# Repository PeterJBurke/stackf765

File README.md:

# StackF765

An open-hardware **ArduPilot flight controller** built around the STM32F765:
two stacked 31.5 × 48 mm boards on a 20 × 20 mm mount, plus a small USB / buzzer / boot
board on a cable. Every connection except the battery and ESC power wires is a labelled 0.1 inch (Dupont) right-angle pin on the upper board: a 3 × 12 header at the front, and a 3 × 9 header at the back for motors, LED and companion-computer power.

**[3D project page](https://peterjburke.github.io/stackf765/)** ·
**[Drone viewer](https://peterjburke.github.io/stackf765/drone/)** ·
[Pinout](docs/pinout.md) · [How it works](docs/design.md) · [Order boards](docs/manufacturing.md) ·
[Assemble](docs/assembly.md) · [First power-up](docs/bringup.md) · [Firmware](docs/firmware.md) ·
[Verification](docs/verification.md)

| Upper board (flight controller) | Lower board (power) | Service board |
|---|---|---|
|  |  |  |

> **Status: design complete and verified by rule checks; no hardware has been built yet.**
> The first boards are prototypes. Use the [first power-up procedure](docs/bringup.md).

## At a glance

| | |
|---|---|
| Processor | STM32F765VIT6, 216 MHz Cortex-M7, 2 MB flash |
| Firmware | ArduPilot (Copter, Plane, Rover), board name `StackF765` |
| Sensors | ICM-45686 IMU (SPI), BMP388 barometer (I2C) |
| Battery | 2S–3S LiPo (6–13 V), 50 A continuous through a 0.5 mΩ shunt |
| Serial | 7 UARTs + USB |
| Outputs | 6 motor/servo outputs on standard 3-pin columns (signal / 5 V / ground), addressable LED |
| Video | Analog OSD (AT7456E), camera in / VTX out |
| Logging | microSD (socket under the upper board, card inserted from the left edge) |
| 5 V rails | 3 A for the flight controller and peripherals, a separate 3 A for a companion computer |
| Size | 31.5 × 48 × about 19 mm, 20 × 20 mm grommet mount |

## Pinout in brief

Front header (upper board), seen from above with the header pointing away from you:

| Row | 1 | 2 | 3 | 4 | 5 | 6 | 7 | 8 | 9 | 10 | 11 | 12 |
|---|---|---|---|---|---|---|---|---|---|---|---|---|
| front edge | G | 5V | TX6 | RX6 | G | 5V | TX7 | RX7 | G | 5V | TX8 | RX8 |
| middle | G | 4V5 | TX2 | RX2 | G | 5V | TX3 | RX3 | G | 5V | TX4 | RX4 |
| inner | G | 4V5 | TX1 | RX1 | SDA | SCL | G | 5V | CAM | G | 5V | VTX |

Rear header (upper board), looking into the pins from behind, columns left to right: `PI5V PI5V M1 M2 M3 M4 M5 M6 LED`; each column is signal / 5 V / ground from top to bottom, so a 3-pin servo plug fits directly. The lower board has no pin header.
Power pads at the rear: `BAT+ ESC+ ESC− BAT−`. Full details: [docs/pinout.md](docs/pinout.md).

## What is in this repository

| Folder | Contents |
|---|---|
| `hardware/` | KiCad 9 projects for the three boards (schematics and routed PCBs), custom footprints and 3D models |
| `fab/` | Gerbers, drill files, bills of materials and placement files, ready to upload |
| `firmware/` | ArduPilot board definition (`hwdef`), build script, prebuilt binaries |
| `docs/` | Documentation, schematic PDFs, renders, and the web pages |
| `gen/` | The Python design files the KiCad projects are generated from, and the generator |
| `tools/` | Verification scripts |
| `research/` | Part selection notes, datasheet checks, and the independent design review |

## How the design is made

The circuits are written as short Python files (`gen/upper.py`, `gen/lower.py`,
`gen/service.py`). `make` turns them into KiCad schematics and boards, places and routes
the parts, fills the copper, runs KiCad's own rule checks, and writes the fabrication files,
renders and web pages. Because one description produces both schematic and board, they cannot
drift apart, and KiCad checks that they match.

You do not need the generator to use the design: open `hardware/<board>/<board>.kicad_pro`
in KiCad 9 and work on it like any other project.

```sh
make            # regenerate everything (needs KiCad 9, Python 3, gcc)
make verify     # run all checks on the committed files
make firmware ARDUPILOT=/path/to/ardupilot
```

## Verification summary

Every board passes KiCad ERC and DRC with zero violations and zero unconnected nets, the
board matches the schematic, the 49 microcontroller pins used by the firmware are cross-checked
against the schematic, the boards are checked to fit together, and ArduPilot builds for the
board. See [docs/verification-report.md](docs/verification-report.md) for the current results
and [docs/verification.md](docs/verification.md) for what those checks do and do not cover.

## Licence

Hardware: [CERN-OHL-P v2](LICENSE-HARDWARE.txt). Software, scripts and documentation: [MIT](LICENSE).
The drone frame model and coin used in the drone viewer are third-party assets; see
`docs/drone/assets/CREDITS.txt`.

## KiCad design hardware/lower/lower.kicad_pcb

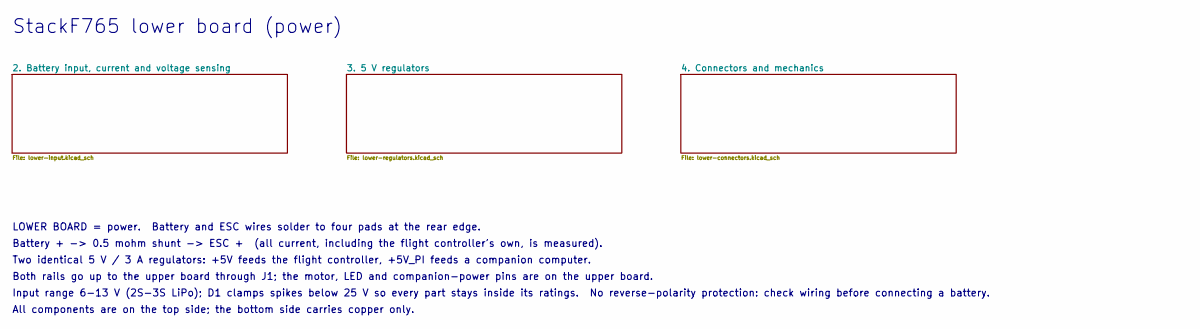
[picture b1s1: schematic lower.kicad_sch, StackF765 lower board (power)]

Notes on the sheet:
StackF765 lower board (power)
LOWER BOARD = power. Battery and ESC wires solder to four pads at the rear edge.
Battery + -> 0.5 mohm shunt -> ESC + (all current, including the flight controller's own, is measured).
Two identical 5 V / 3 A regulators: +5V feeds the flight controller, +5V_PI feeds a companion computer.
Both rails go up to the upper board through J1; the motor, LED and companion-power pins are on the upper board.
Input range 6-13 V (2S-3S LiPo); D1 clamps spikes below 25 V so every part stays inside its ratings. No reverse-polarity protection: check wiring before connecting a battery.
All components are on the top side; the bottom side carries copper only.

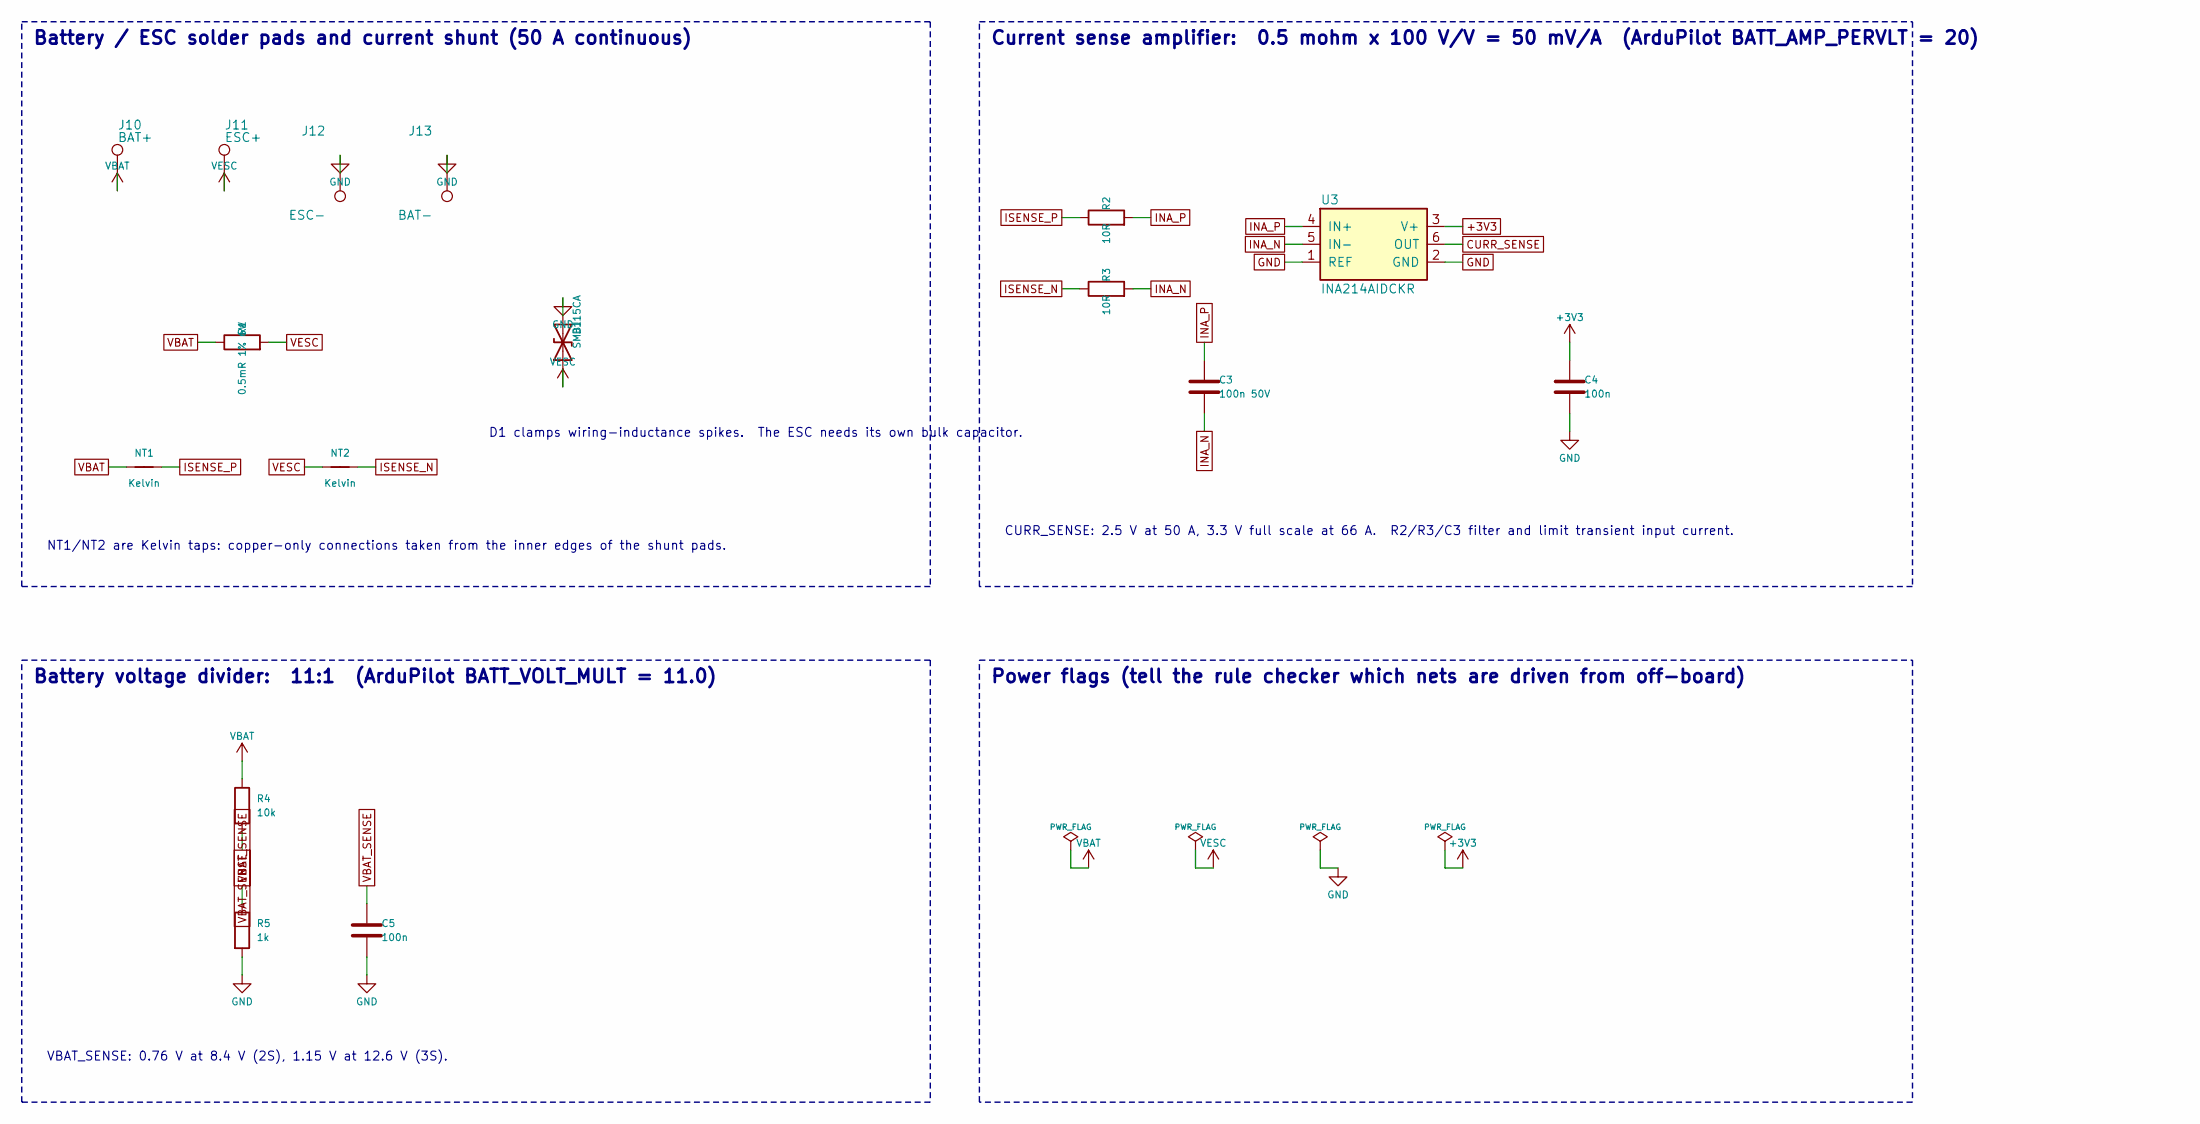
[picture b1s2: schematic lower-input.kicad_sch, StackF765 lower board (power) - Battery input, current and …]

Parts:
C3: 100n 50V; C_0402_1005Metric; MPN GRM155R71H104KE14D; LCSC C77020
C4, C5: 100n; C_0402_1005Metric; MPN CL05B104KO5NNNC; LCSC C1525
D1: SMBJ15CA; D_SMB; MPN SMBJ15CA; LCSC C169449
J10: BAT+; WirePad_5x4mm
J11: ESC+; WirePad_5x4mm
J12: ESC-; WirePad_5x4mm
J13: BAT-; WirePad_5x4mm
NT1, NT2: Kelvin; NetTie-2_SMD_Pad0.5mm
R1: 0.5mR 1% 6W; R_Shunt_2512_ASR-M-3; MPN ASR-M-3-0.5F; LCSC C469426
R2, R3: 10R; R_0402_1005Metric; MPN 0402WGF100JTCE; LCSC C25077
R4: 10k; R_0402_1005Metric; MPN 0402WGF1002TCE; LCSC C25744
R5: 1k; R_0402_1005Metric; MPN 0402WGF1001TCE; LCSC C11702
U3: INA214AIDCKR; SOT-363_SC-70-6; MPN INA214AIDCKR; LCSC C105240

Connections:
+3V3: C4.1, U3.3 (V+); also elsewhere on the board
CURR_SENSE: U3.6 (OUT); also elsewhere on the board
GND: C4.2, C5.2, D1.2 (A2), J12.1, J13.1, R5.2, U3.1 (REF), U3.2 (GND); also elsewhere on the board
INA_N: C3.2, R3.2, U3.5 (IN-)
INA_P: C3.1, R2.2, U3.4 (IN+)
ISENSE_N: NT2.2, R3.1
ISENSE_P: NT1.2, R2.1
VBAT: J10.1, NT1.1, R1.1, R4.1
VBAT_SENSE: C5.1, R4.2, R5.1; also elsewhere on the board
VESC: D1.1 (A1), J11.1, NT2.1, R1.2; also elsewhere on the board

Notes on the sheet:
Battery / ESC solder pads and current shunt (50 A continuous)
NT1/NT2 are Kelvin taps: copper-only connections taken from the inner edges of the shunt pads.
D1 clamps wiring-inductance spikes. The ESC needs its own bulk capacitor.
Current sense amplifier: 0.5 mohm x 100 V/V = 50 mV/A (ArduPilot BATT_AMP_PERVLT = 20)
CURR_SENSE: 2.5 V at 50 A, 3.3 V full scale at 66 A. R2/R3/C3 filter and limit transient input current.
Battery voltage divider: 11:1 (ArduPilot BATT_VOLT_MULT = 11.0)
VBAT_SENSE: 0.76 V at 8.4 V (2S), 1.15 V at 12.6 V (3S).
Power flags (tell the rule checker which nets are driven from off-board)

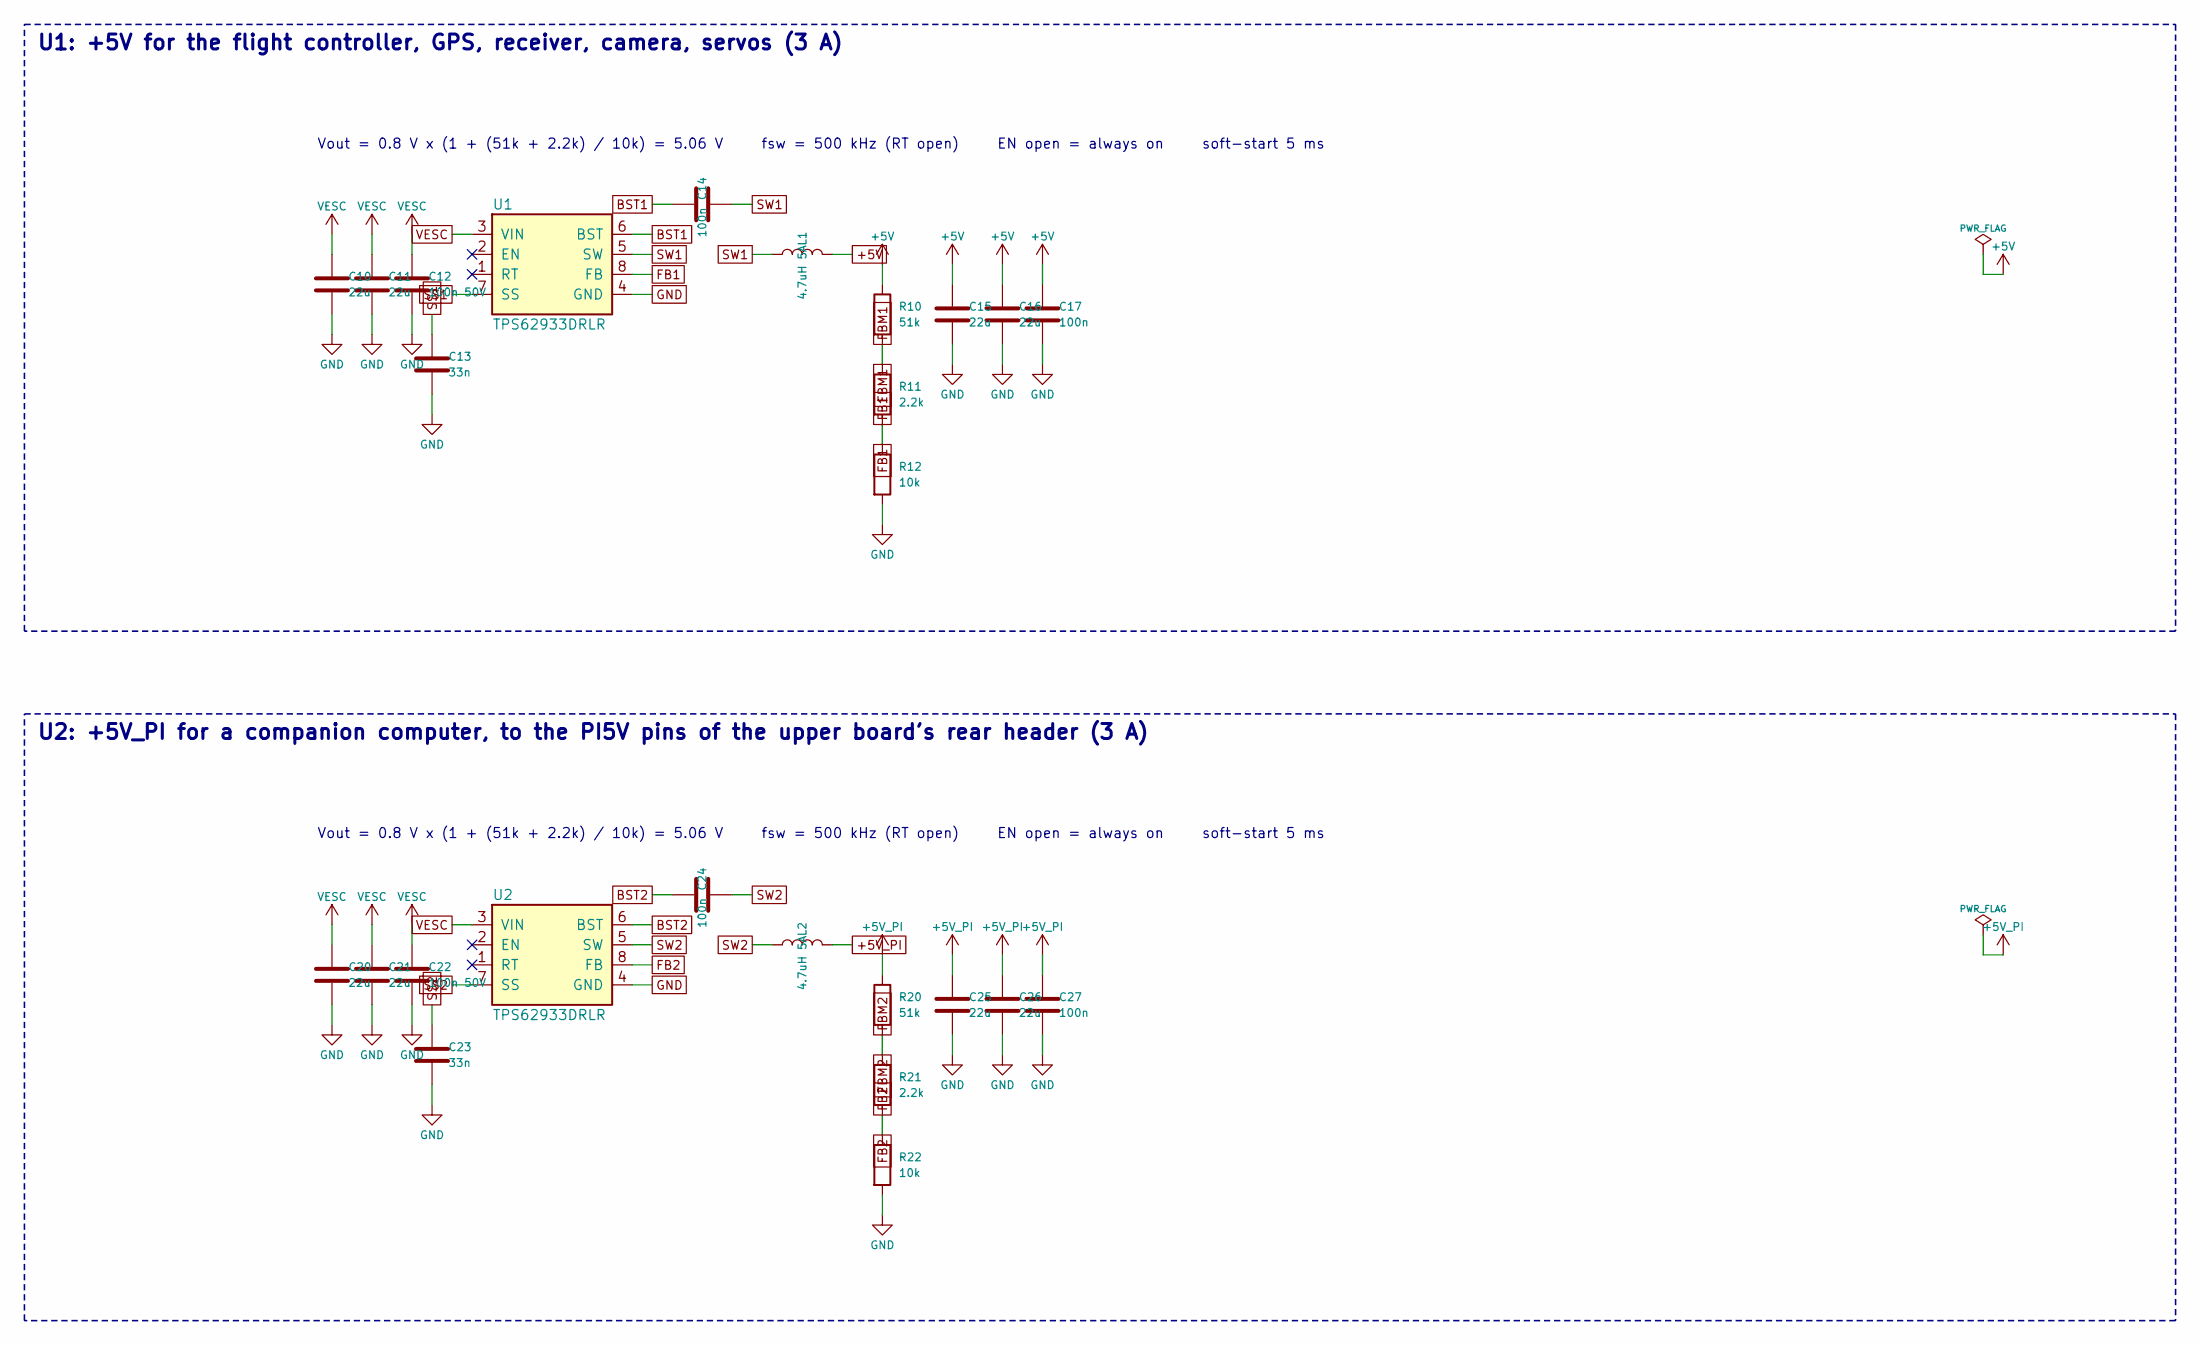
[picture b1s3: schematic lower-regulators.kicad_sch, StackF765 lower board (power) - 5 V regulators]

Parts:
C10, C11, C20, C21: 22u; C_1206_3216Metric; MPN CL31A226KAHNNNE; LCSC C12891
C12, C22: 100n 50V; C_0402_1005Metric; MPN GRM155R71H104KE14D; LCSC C77020
C13, C23: 33n; C_0402_1005Metric; MPN CC0402KRX7R9BB333; LCSC C106862
C14, C17, C24, C27: 100n; C_0402_1005Metric; MPN CL05B104KO5NNNC; LCSC C1525
C15, C16, C25, C26: 22u; C_0805_2012Metric; MPN CL21A226MAQNNNE; LCSC C45783
L1, L2: 4.7uH 5A; L_SXN_SMMS0530; MPN SMMS0530-4R7M; LCSC C181722
R10, R20: 51k; R_0402_1005Metric; MPN 0402WGF5102TCE; LCSC C25794
R11, R21: 2.2k; R_0402_1005Metric; MPN 0402WGF2201TCE; LCSC C25879
R12, R22: 10k; R_0402_1005Metric; MPN 0402WGF1002TCE; LCSC C25744
U1, U2: TPS62933DRLR; SOT-583-8; MPN TPS62933DRLR; LCSC C3200405

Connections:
+5V: C15.1, C16.1, C17.1, L1.2, R10.1; also elsewhere on the board
+5V_PI: C25.1, C26.1, C27.1, L2.2, R20.1; also elsewhere on the board
BST1: C14.1, U1.6 (BST)
BST2: C24.1, U2.6 (BST)
FB1: R11.2, R12.1, U1.8 (FB)
FB2: R21.2, R22.1, U2.8 (FB)
FBM1: R10.2, R11.1
FBM2: R20.2, R21.1
GND: C10.2, C11.2, C12.2, C13.2, C15.2, C16.2, C17.2, C20.2, C21.2, C22.2, C23.2, C25.2, C26.2, C27.2, R12.2, R22.2, U1.4 (GND), U2.4 (GND); also elsewhere on the board
SS1: C13.1, U1.7 (SS)
SS2: C23.1, U2.7 (SS)
SW1: C14.2, L1.1, U1.5 (SW)
SW2: C24.2, L2.1, U2.5 (SW)
VESC: C10.1, C11.1, C12.1, C20.1, C21.1, C22.1, U1.3 (VIN), U2.3 (VIN); also elsewhere on the board

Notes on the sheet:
U1: +5V for the flight controller, GPS, receiver, camera, servos (3 A)
Vout = 0.8 V x (1 + (51k + 2.2k) / 10k) = 5.06 V fsw = 500 kHz (RT open) EN open = always on soft-start 5 ms
U2: +5V_PI for a companion computer, to the PI5V pins of the upper board's rear header (3 A)

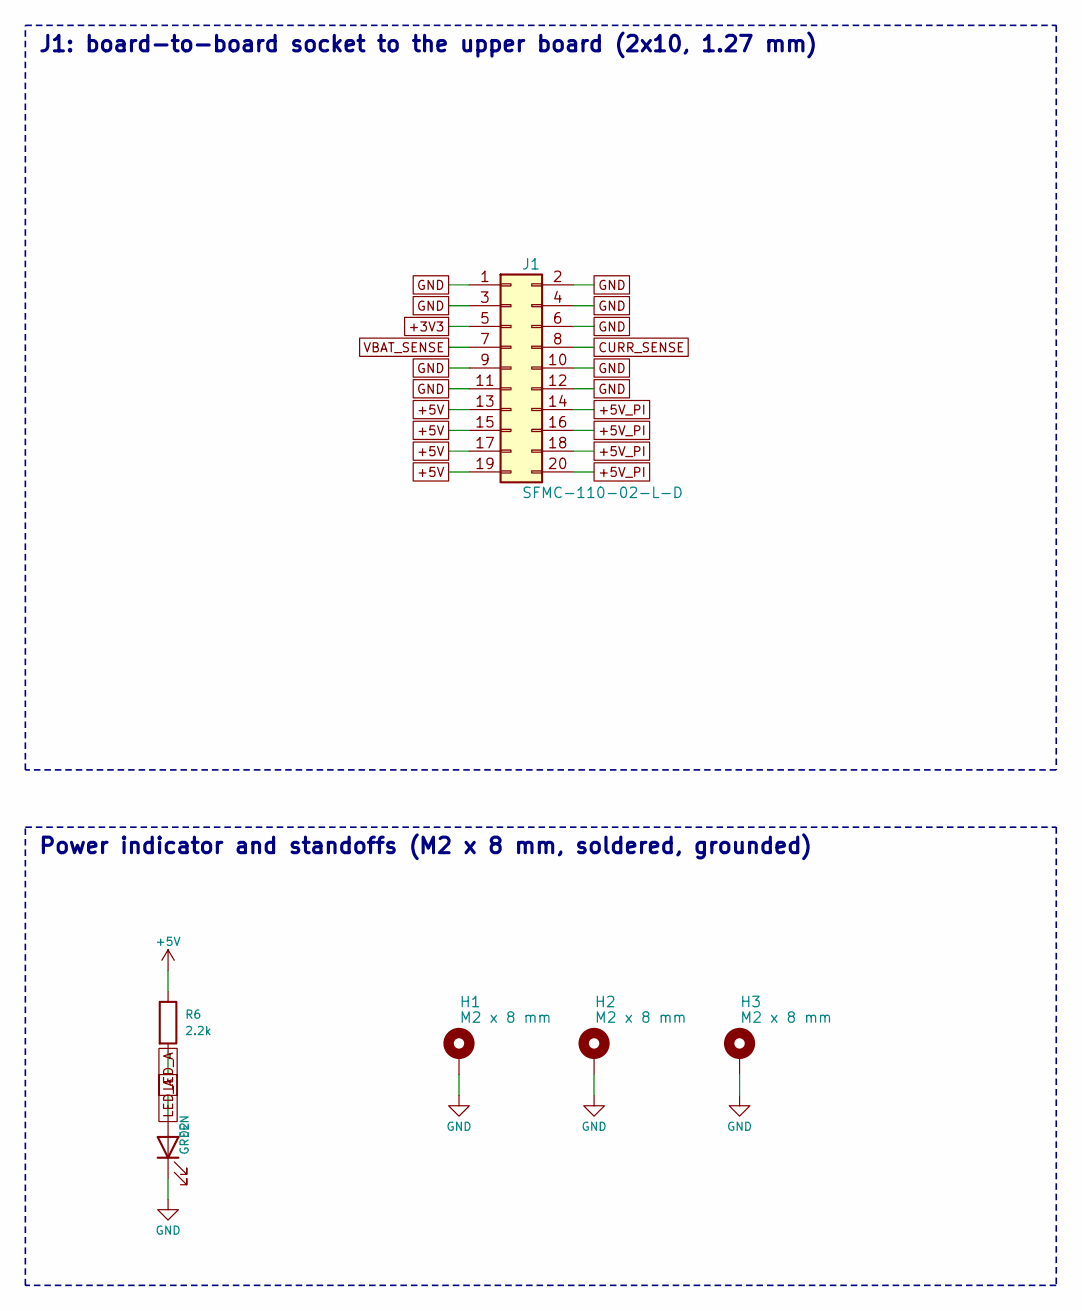
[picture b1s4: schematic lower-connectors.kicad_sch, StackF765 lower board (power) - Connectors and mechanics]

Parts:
D2: GREEN; LED_0603_1608Metric; MPN NCD0603G1; LCSC C84267
H1, H2, H3: M2 x 8 mm; Standoff_SMT_M2_H8.0; MPN SMTSO2080CTJ; LCSC C2916357
J1: SFMC-110-02-L-D; Samtec_SFMC-110-02-x-D; MPN SFMC-110-02-L-D-K-TR; LCSC C3323057
R6: 2.2k; R_0402_1005Metric; MPN 0402WGF2201TCE; LCSC C25879

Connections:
+3V3: J1.5; also elsewhere on the board
+5V: J1.13, J1.15, J1.17, J1.19, R6.1; also elsewhere on the board
+5V_PI: J1.14, J1.16, J1.18, J1.20; also elsewhere on the board
CURR_SENSE: J1.8; also elsewhere on the board
GND: D2.1 (K), H1.1, H2.1, H3.1, J1.1, J1.2, J1.3, J1.4, J1.6, J1.9, J1.10, J1.11, J1.12; also elsewhere on the board
LED_A: D2.2 (A), R6.2
VBAT_SENSE: J1.7; also elsewhere on the board

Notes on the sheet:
J1: board-to-board socket to the upper board (2x10, 1.27 mm)
Power indicator and standoffs (M2 x 8 mm, soldered, grounded)

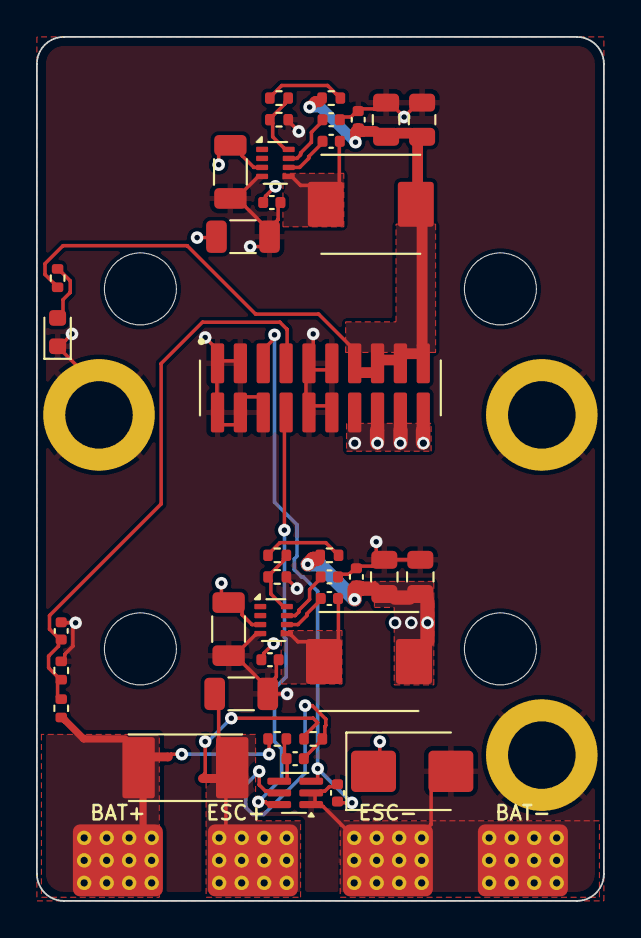
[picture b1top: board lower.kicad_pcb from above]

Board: 4 copper layers, 31.5 x 48.0 mm, 52 parts (0 on the bottom side), 23 nets.

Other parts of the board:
H: (no value)
H#2, H#3, H#4: (no value)

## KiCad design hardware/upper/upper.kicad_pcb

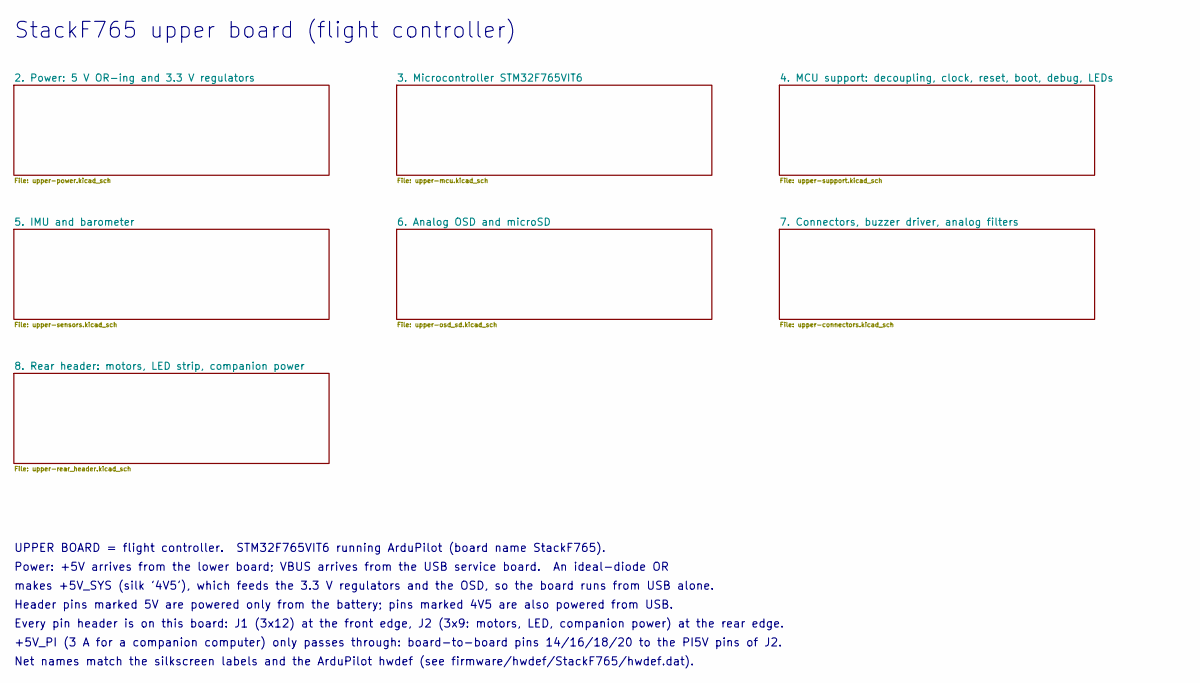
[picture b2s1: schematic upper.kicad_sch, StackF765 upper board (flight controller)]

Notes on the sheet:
StackF765 upper board (flight controller)
UPPER BOARD = flight controller. STM32F765VIT6 running ArduPilot (board name StackF765).
Power: +5V arrives from the lower board; VBUS arrives from the USB service board. An ideal-diode OR
makes +5V_SYS (silk '4V5'), which feeds the 3.3 V regulators and the OSD, so the board runs from USB alone.
Header pins marked 5V are powered only from the battery; pins marked 4V5 are also powered from USB.
Every pin header is on this board: J1 (3x12) at the front edge, J2 (3x9: motors, LED, companion power) at the rear edge.
+5V_PI (3 A for a companion computer) only passes through: board-to-board pins 14/16/18/20 to the PI5V pins of J2.
Net names match the silkscreen labels and the ArduPilot hwdef (see firmware/hwdef/StackF765/hwdef.dat).

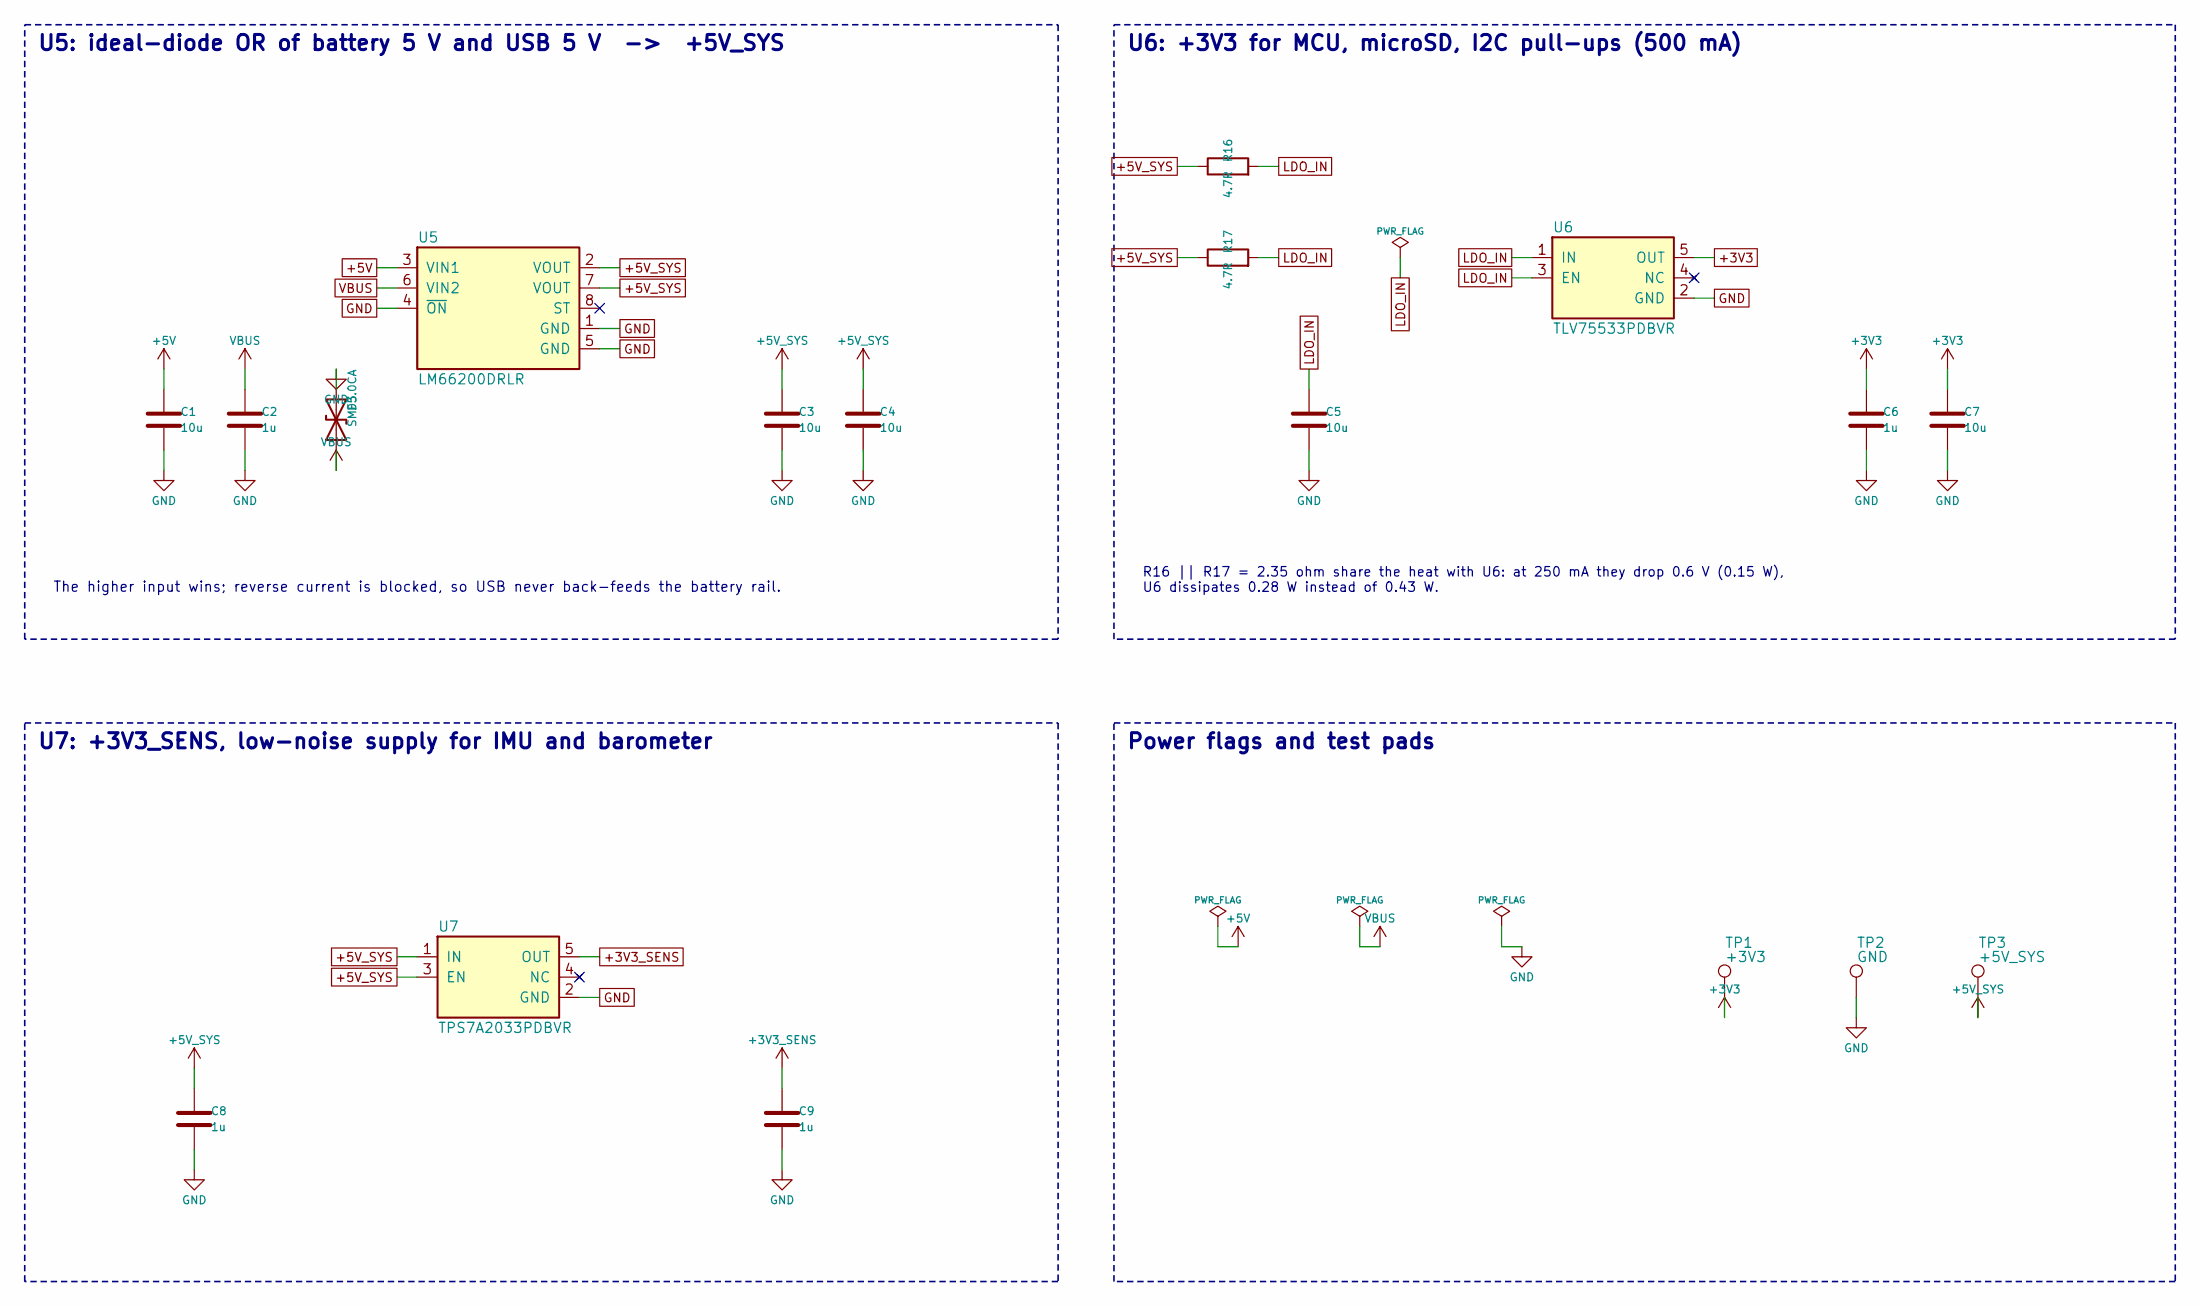
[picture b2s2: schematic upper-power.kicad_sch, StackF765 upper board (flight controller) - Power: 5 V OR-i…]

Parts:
C1, C3, C4, C5, C7: 10u; C_0603_1608Metric; MPN CL10A106MA8NRNC; LCSC C96446
C2, C6, C8, C9: 1u; C_0402_1005Metric; MPN CL05A105KA5NQNC; LCSC C52923
D3: SMF5.0CA; D_SOD-123F; MPN SMF5.0CA-TP; LCSC C914432
R16, R17: 4.7R; R_1206_3216Metric; MPN HP06W2F470KT5E; LCSC C414936
TP1: +3V3; TestPoint_Pad_D1.0mm
TP2: GND; TestPoint_Pad_D1.0mm
TP3: +5V_SYS; TestPoint_Pad_D1.0mm
U5: LM66200DRLR; SOT-583-8; MPN LM66200DRLR; LCSC C3235556
U6: TLV75533PDBVR; SOT-23-5; MPN TLV75533PDBVR; LCSC C404027
U7: TPS7A2033PDBVR; SOT-23-5; MPN TPS7A2033PDBVR; LCSC C2862740

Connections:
+3V3: C6.1, C7.1, TP1.1, U6.5 (OUT); also elsewhere on the board
+3V3_SENS: C9.1, U7.5 (OUT); also elsewhere on the board
+5V: C1.1, U5.3 (VIN1); also elsewhere on the board
+5V_SYS: C3.1, C4.1, C8.1, R16.1, R17.1, TP3.1, U5.2 (VOUT), U5.7 (VOUT), U7.1 (IN), U7.3 (EN); also elsewhere on the board
GND: C1.2, C2.2, C3.2, C4.2, C5.2, C6.2, C7.2, C8.2, C9.2, D3.2 (A2), TP2.1, U5.1 (GND), U5.4 (~ON), U5.5 (GND), U6.2 (GND), U7.2 (GND); also elsewhere on the board
LDO_IN: C5.1, R16.2, R17.2, U6.1 (IN), U6.3 (EN)
VBUS: C2.1, D3.1 (A1), U5.6 (VIN2); also elsewhere on the board

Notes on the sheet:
U5: ideal-diode OR of battery 5 V and USB 5 V -> +5V_SYS
The higher input wins; reverse current is blocked, so USB never back-feeds the battery rail.
U6: +3V3 for MCU, microSD, I2C pull-ups (500 mA)
R16 || R17 = 2.35 ohm share the heat with U6: at 250 mA they drop 0.6 V (0.15 W), U6 dissipates 0.28 W instead of 0.43 W.
U7: +3V3_SENS, low-noise supply for IMU and barometer
Power flags and test pads

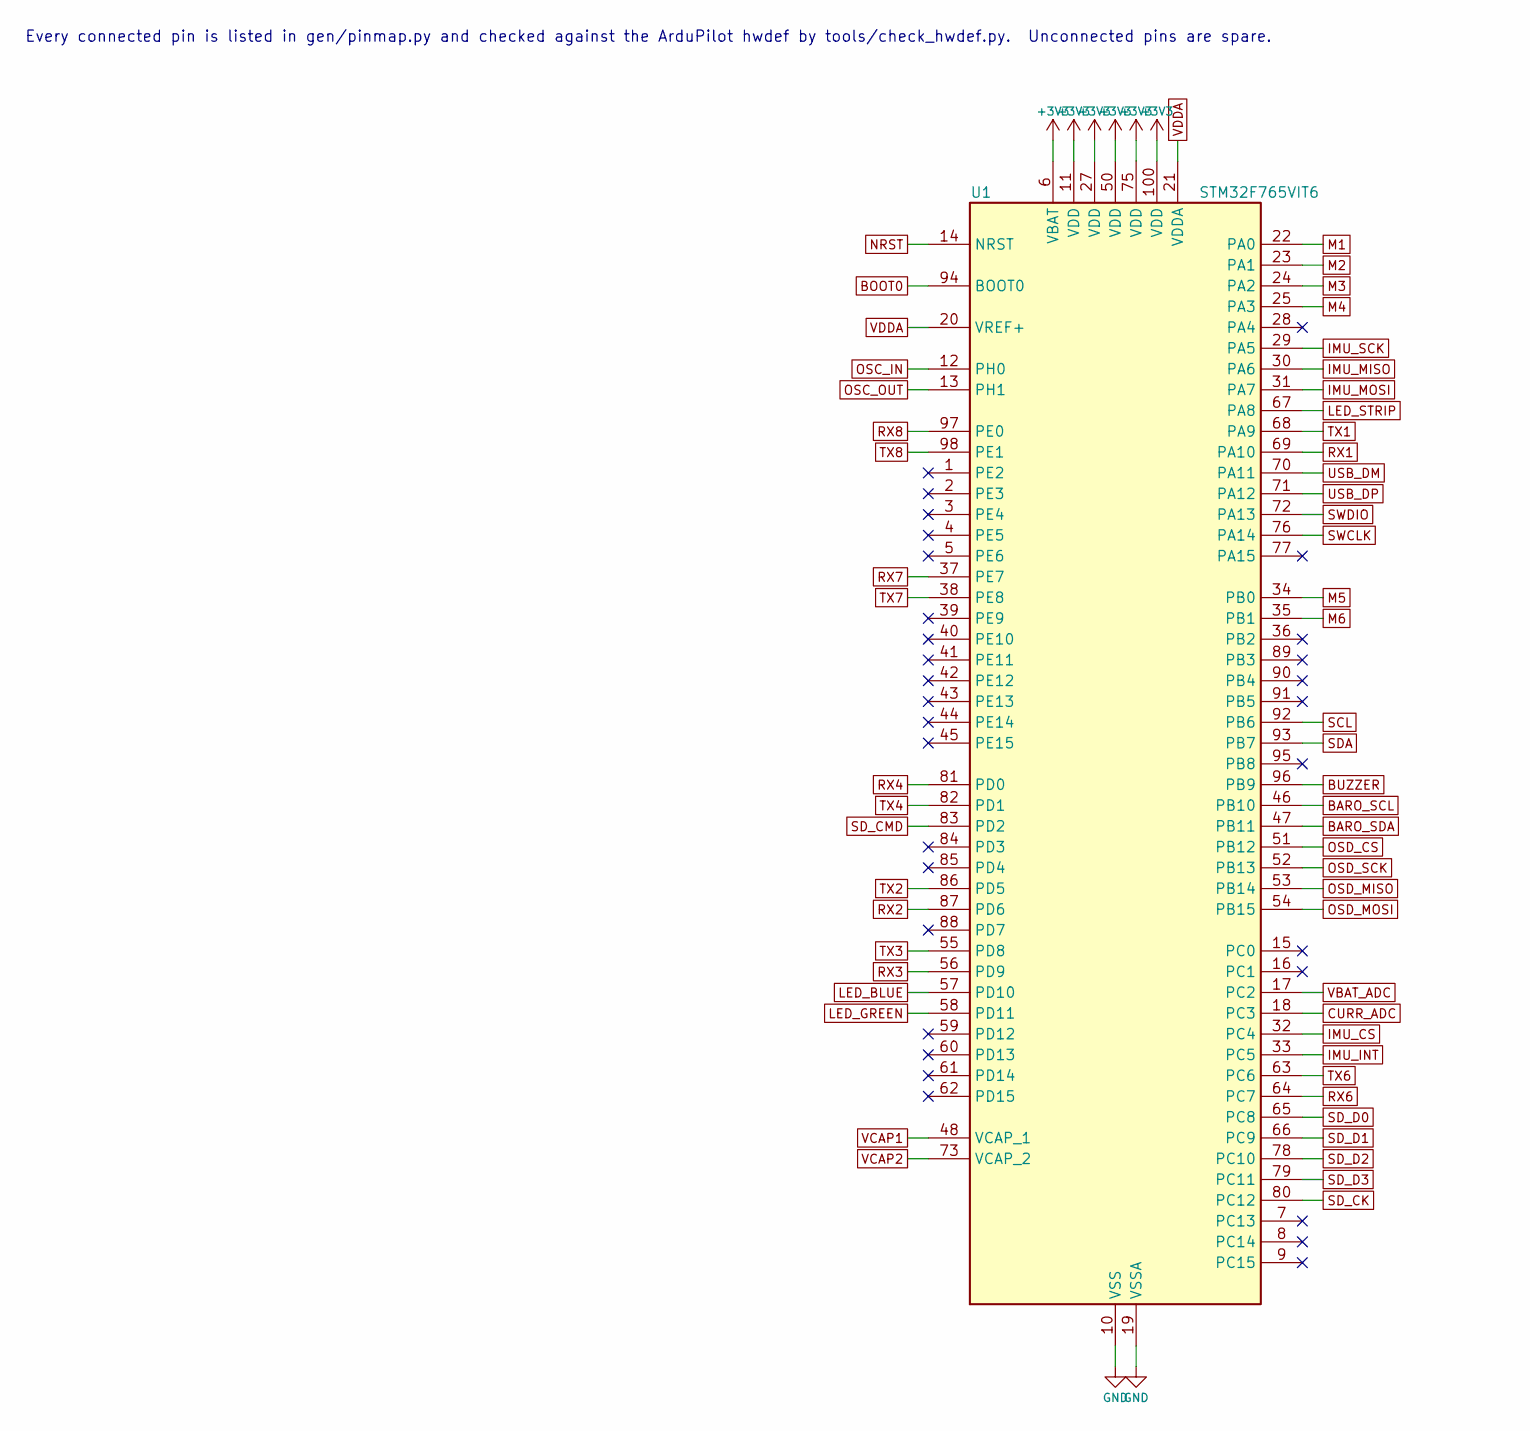
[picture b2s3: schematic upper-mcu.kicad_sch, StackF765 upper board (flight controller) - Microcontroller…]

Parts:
U1: STM32F765VIT6; LQFP-100_14x14mm_P0.5mm; MPN STM32F765VIT6; LCSC C710319

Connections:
+3V3: U1.6 (VBAT), U1.11 (VDD), U1.27 (VDD), U1.50 (VDD), U1.75 (VDD), U1.100 (VDD); also elsewhere on the board
BARO_SCL: U1.46 (PB10); also elsewhere on the board
BARO_SDA: U1.47 (PB11); also elsewhere on the board
BOOT0: U1.94 (BOOT0); also elsewhere on the board
BUZZER: U1.96 (PB9); also elsewhere on the board
CURR_ADC: U1.18 (PC3); also elsewhere on the board
GND: U1.10 (VSS), U1.19 (VSSA), U1.26 (VSS), U1.49 (VSS), U1.74 (VSS), U1.99 (VSS); also elsewhere on the board
IMU_CS: U1.32 (PC4); also elsewhere on the board
IMU_INT: U1.33 (PC5); also elsewhere on the board
IMU_MISO: U1.30 (PA6); also elsewhere on the board
IMU_MOSI: U1.31 (PA7); also elsewhere on the board
IMU_SCK: U1.29 (PA5); also elsewhere on the board
LED_BLUE: U1.57 (PD10); also elsewhere on the board
LED_GREEN: U1.58 (PD11); also elsewhere on the board
LED_STRIP: U1.67 (PA8); also elsewhere on the board
M1: U1.22 (PA0); also elsewhere on the board
M2: U1.23 (PA1); also elsewhere on the board
M3: U1.24 (PA2); also elsewhere on the board
M4: U1.25 (PA3); also elsewhere on the board
M5: U1.34 (PB0); also elsewhere on the board
M6: U1.35 (PB1); also elsewhere on the board
NRST: U1.14 (NRST); also elsewhere on the board
OSC_IN: U1.12 (PH0); also elsewhere on the board
OSC_OUT: U1.13 (PH1); also elsewhere on the board
OSD_CS: U1.51 (PB12); also elsewhere on the board
OSD_MISO: U1.53 (PB14); also elsewhere on the board
OSD_MOSI: U1.54 (PB15); also elsewhere on the board
OSD_SCK: U1.52 (PB13); also elsewhere on the board
RX1: U1.69 (PA10); also elsewhere on the board
RX2: U1.87 (PD6); also elsewhere on the board
RX3: U1.56 (PD9); also elsewhere on the board
RX4: U1.81 (PD0); also elsewhere on the board
RX6: U1.64 (PC7); also elsewhere on the board
RX7: U1.37 (PE7); also elsewhere on the board
RX8: U1.97 (PE0); also elsewhere on the board
SCL: U1.92 (PB6); also elsewhere on the board
SDA: U1.93 (PB7); also elsewhere on the board
SD_CK: U1.80 (PC12); also elsewhere on the board
SD_CMD: U1.83 (PD2); also elsewhere on the board
SD_D0: U1.65 (PC8); also elsewhere on the board
SD_D1: U1.66 (PC9); also elsewhere on the board
SD_D2: U1.78 (PC10); also elsewhere on the board
SD_D3: U1.79 (PC11); also elsewhere on the board
SWCLK: U1.76 (PA14); also elsewhere on the board
SWDIO: U1.72 (PA13); also elsewhere on the board
TX1: U1.68 (PA9); also elsewhere on the board
TX2: U1.86 (PD5); also elsewhere on the board
TX3: U1.55 (PD8); also elsewhere on the board
TX4: U1.82 (PD1); also elsewhere on the board
TX6: U1.63 (PC6); also elsewhere on the board
TX7: U1.38 (PE8); also elsewhere on the board
TX8: U1.98 (PE1); also elsewhere on the board
USB_DM: U1.70 (PA11); also elsewhere on the board
USB_DP: U1.71 (PA12); also elsewhere on the board
VBAT_ADC: U1.17 (PC2); also elsewhere on the board
VCAP1: U1.48 (VCAP_1); also elsewhere on the board
VCAP2: U1.73 (VCAP_2); also elsewhere on the board
VDDA: U1.20 (VREF+), U1.21 (VDDA); also elsewhere on the board

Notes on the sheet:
Every connected pin is listed in gen/pinmap.py and checked against the ArduPilot hwdef by tools/check_hwdef.py. Unconnected pins are spare.
